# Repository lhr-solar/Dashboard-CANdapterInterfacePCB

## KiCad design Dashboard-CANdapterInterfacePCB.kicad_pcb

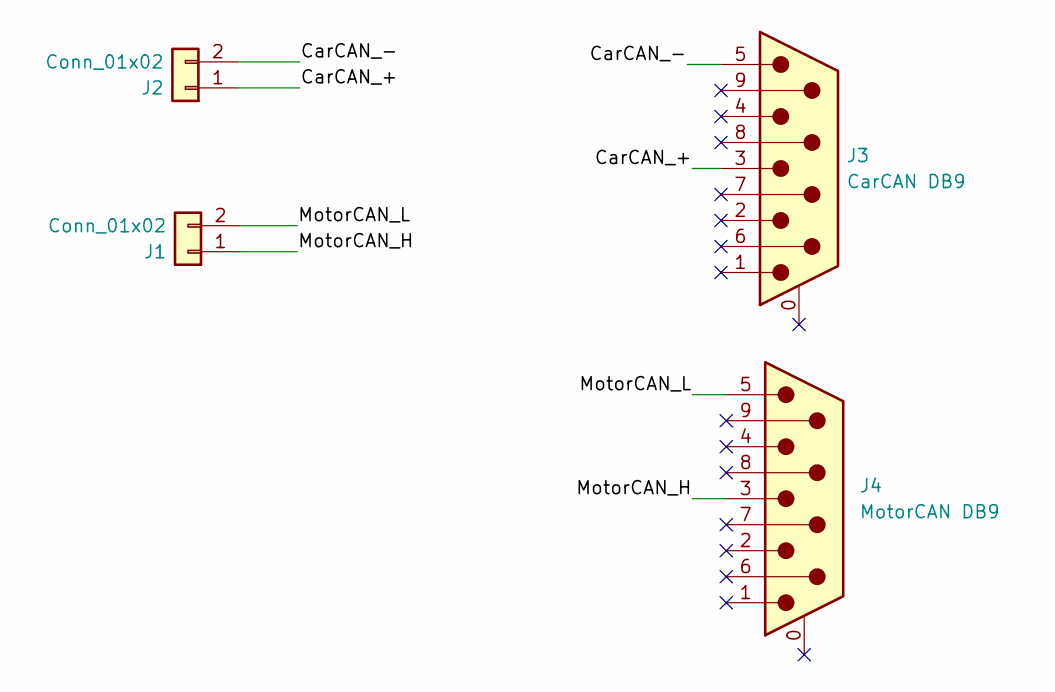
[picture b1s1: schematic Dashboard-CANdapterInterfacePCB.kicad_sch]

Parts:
J1, J2: Conn_01x02; Molex_Micro-Fit_3.0_43650-0215_1x02_P3.00mm_Vertical
J3: CarCAN DB9; AMPHENOL_L77SDE09SA4CH3R
J4: MotorCAN DB9; AMPHENOL_L77SDE09SA4CH3R

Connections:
/CarCAN_+: J2.1, J3.3
/CarCAN_-: J2.2, J3.5
/MotorCAN_+: J1.1, J4.3
/MotorCAN_-: J1.2, J4.5

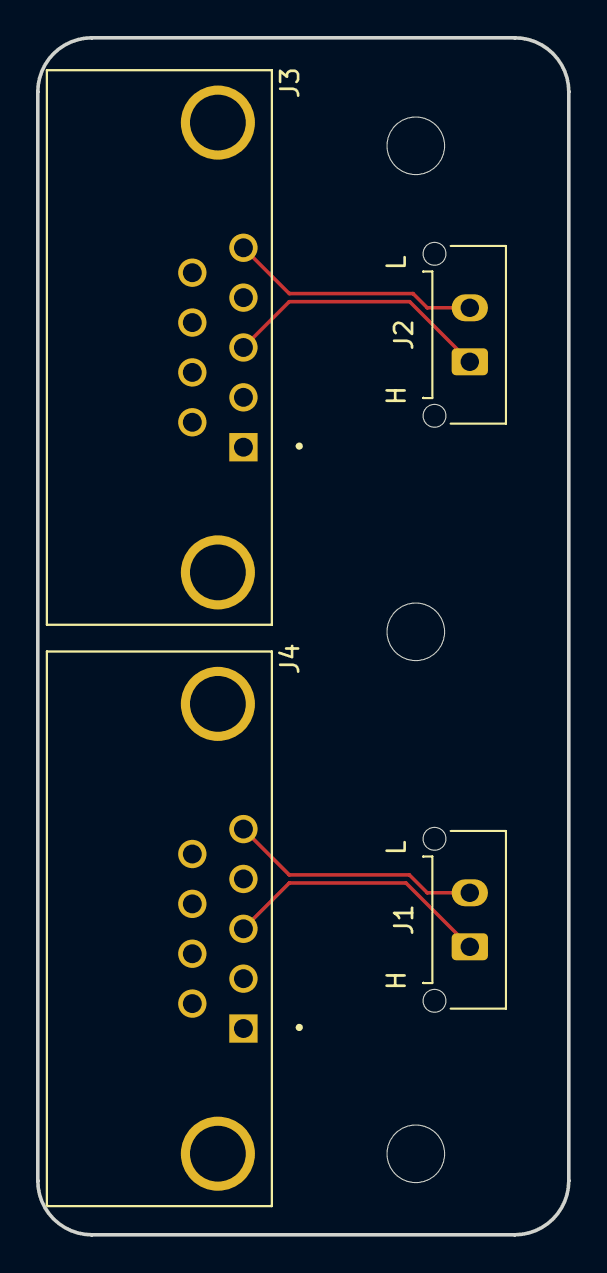
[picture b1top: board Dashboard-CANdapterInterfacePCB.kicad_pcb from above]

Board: 2 copper layers, 29.5 x 66.5 mm, 4 parts (0 on the bottom side), 4 nets.

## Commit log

2025-02-10 schem + pcb
